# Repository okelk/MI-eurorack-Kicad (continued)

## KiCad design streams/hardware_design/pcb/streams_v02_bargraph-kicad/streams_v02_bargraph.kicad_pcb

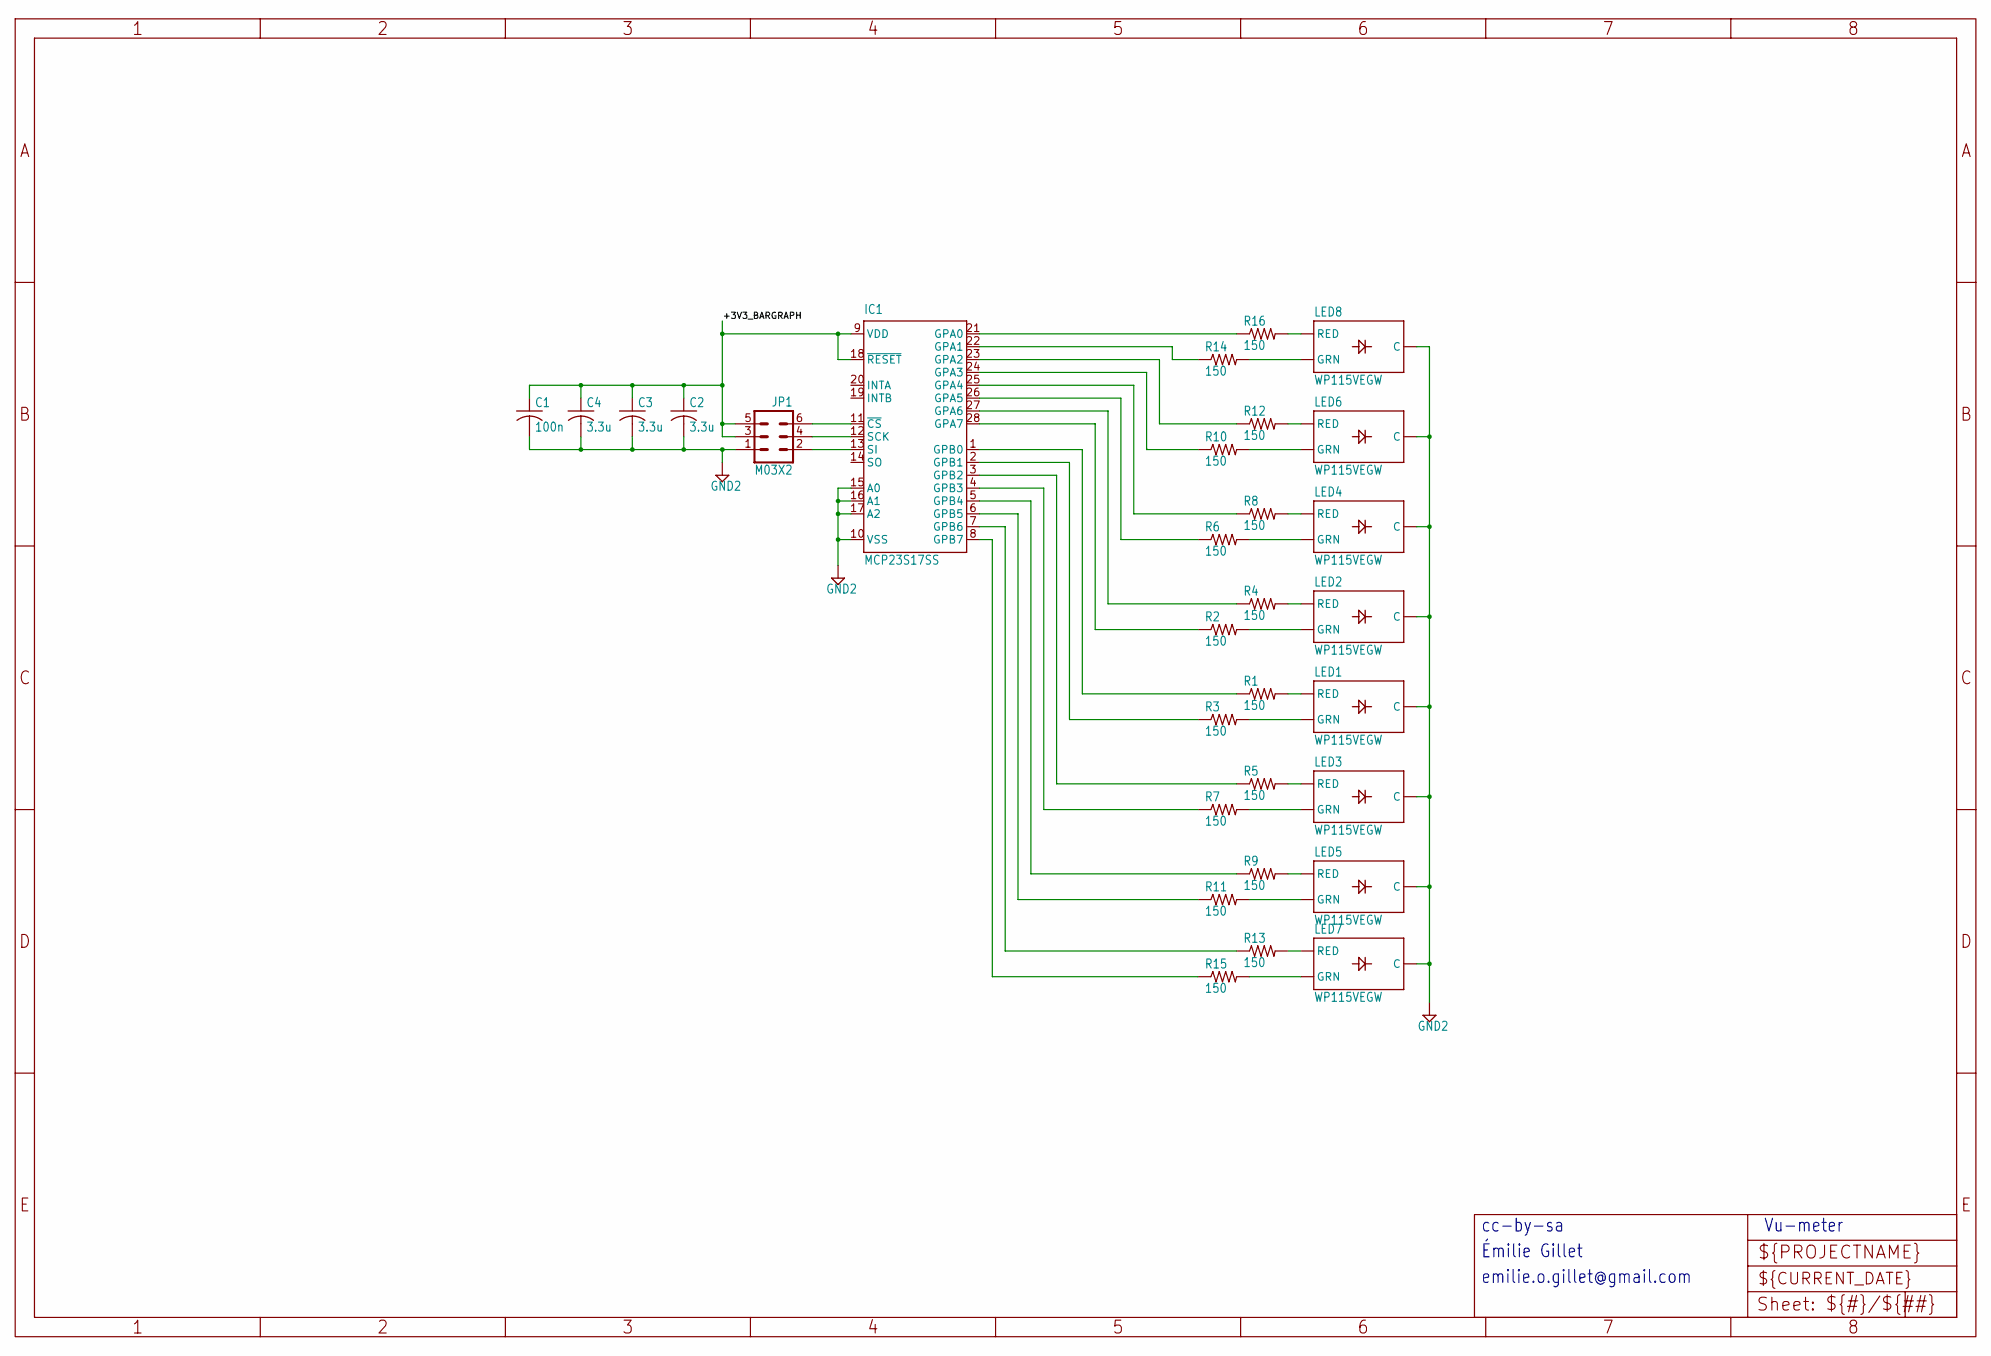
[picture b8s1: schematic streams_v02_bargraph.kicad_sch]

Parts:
C1: 100n; C0603
C2, C3, C4: 3.3u; C0603
IC1: MCP23S17SS; SSOP28
JP1: M03X2; 2X3
LED1, LED2, LED3, LED4, LED5, LED6, LED7, LED8: WP115VEGW; LED-BICOLOR-THROUGHHOLE
R1, R2, R3, R4, R5, R6, R7, R8, R9, R10, R11, R12, R13, R14, R15, R16: 150; R0603

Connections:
+3V3_BARGRAPH: C1.1, C2.1, C3.1, C4.1, IC1.9 (VDD), IC1.18 (~RESET), JP1.3, JP1.5
GND2: C1.2, C2.2, C3.2, C4.2, IC1.10 (VSS), IC1.15 (A0), IC1.16 (A1), IC1.17 (A2), JP1.1, LED1.2 (C), LED2.2 (C), LED3.2 (C), LED4.2 (C), LED5.2 (C), LED6.2 (C), LED7.2 (C), LED8.2 (C)
unnamed: IC1.11 (~CS), JP1.6
unnamed: IC1.12 (SCK), JP1.4
unnamed: LED1.3 (RED), R1.2
unnamed: IC1.13 (SI), JP1.2
unnamed: LED1.1 (GRN), R3.2
unnamed: LED3.3 (RED), R5.2
unnamed: LED3.1 (GRN), R7.2
unnamed: LED5.3 (RED), R9.2
unnamed: LED5.1 (GRN), R11.2
unnamed: LED7.3 (RED), R13.2
unnamed: LED7.1 (GRN), R15.2
unnamed: LED8.3 (RED), R16.2
unnamed: LED8.1 (GRN), R14.2
unnamed: LED6.3 (RED), R12.2
unnamed: LED6.1 (GRN), R10.2
unnamed: LED4.3 (RED), R8.2
unnamed: LED4.1 (GRN), R6.2
unnamed: LED2.3 (RED), R4.2
unnamed: LED2.1 (GRN), R2.2
unnamed: IC1.27 (GPA6), R4.1
unnamed: IC1.28 (GPA7), R2.1
unnamed: IC1.1 (GPB0), R1.1
unnamed: IC1.2 (GPB1), R3.1
unnamed: IC1.21 (GPA0), R16.1
unnamed: IC1.22 (GPA1), R14.1
unnamed: IC1.23 (GPA2), R12.1
unnamed: IC1.24 (GPA3), R10.1
unnamed: IC1.25 (GPA4), R8.1
unnamed: IC1.26 (GPA5), R6.1
unnamed: IC1.3 (GPB2), R5.1
unnamed: IC1.4 (GPB3), R7.1
unnamed: IC1.5 (GPB4), R9.1
unnamed: IC1.6 (GPB5), R11.1
unnamed: IC1.7 (GPB6), R13.1
unnamed: IC1.8 (GPB7), R15.1

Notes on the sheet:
cc-by-sa
Vu-meter
Émilie Gillet
emilie.o.gillet@gmail.com

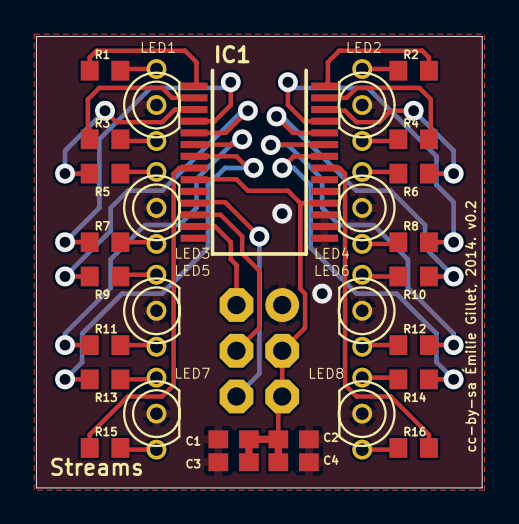
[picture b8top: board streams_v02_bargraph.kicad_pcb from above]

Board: 2 copper layers, 24.8 x 25.1 mm, 30 parts (1 on the bottom side), 37 nets.

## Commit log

2026-06-03 added original versions
    added versions of pre-2020 rippes, shades,veils and pre-2018 tides
2026-06-03 added kicad 7 files
2026-06-03 comment oval holes
2026-06-03 added kicad files
    converted with Kicad 10. Auto-match layers
